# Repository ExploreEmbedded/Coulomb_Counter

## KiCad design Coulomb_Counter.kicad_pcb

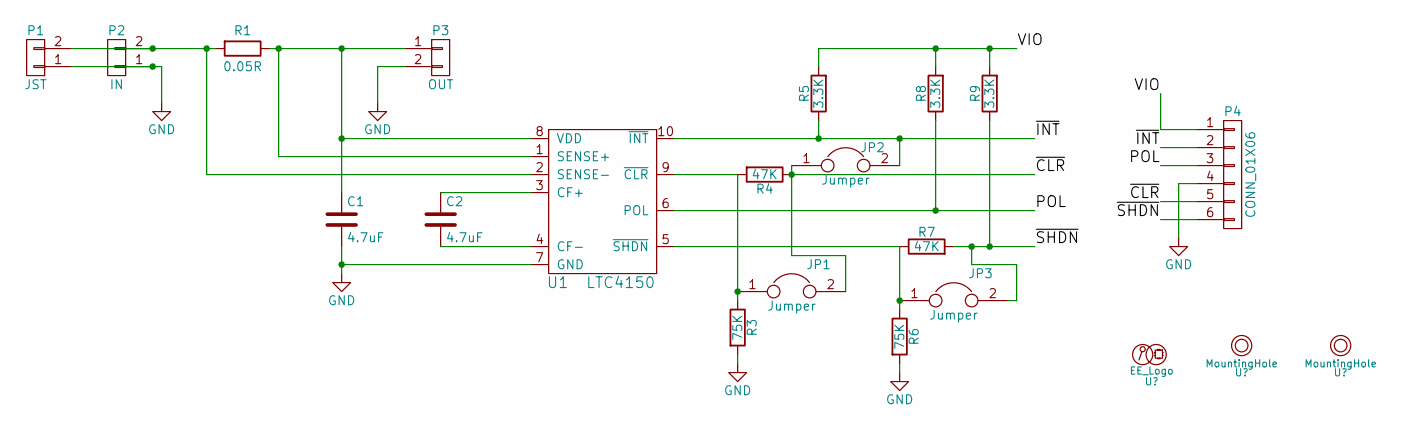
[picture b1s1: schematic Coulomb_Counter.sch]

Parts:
C1, C2: 4.7uF; C_0603
JP1, JP2, JP3: Jumper; SMD_Jumper
P1: JST; JST_Connector_SMD
P2: IN; 2Pin_Jumper_ThroughHole
P3: OUT; 2Pin_Jumper_ThroughHole
P4: CONN_01X06; 6Pin_Burgstick
R1: 0.05R; R_1206
R3, R6: 75K; R_0603
R4, R7: 47K; R_0603
R5, R8, R9: 3.3K; R_0603
U1: LTC4150; MSOP-10_3x3mm_Pitch0.5mm

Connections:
/POL: P4.3, R8.1, U1.6 (POL)
/VIO: P4.1, R5.2, R8.2, R9.2
/~CLR: JP1.2, JP2.1, P4.5, R4.1
/~INT: JP2.2, P4.2, R5.1, U1.10 (~INT)
/~SHDN: JP3.2, P4.6, R7.2, R9.1
GND: C1.2, P1.1, P2.1, P3.2, P4.4, R3.2, R6.2, U1.7 (GND)
unnamed: C1.1, P3.1, R1.1, U1.1 (SENSE+), U1.8 (VDD)
unnamed: C2.1, U1.3 (CF+)
unnamed: C2.2, U1.4 (CF-)
unnamed: JP1.1, R3.1, R4.2, U1.9 (~CLR)
unnamed: JP3.1, R6.1, R7.1, U1.5 (~SHDN)
unnamed: P1.2, P2.2, R1.2, U1.2 (SENSE-)

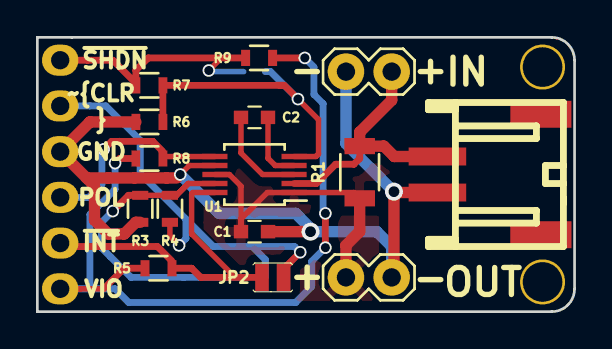
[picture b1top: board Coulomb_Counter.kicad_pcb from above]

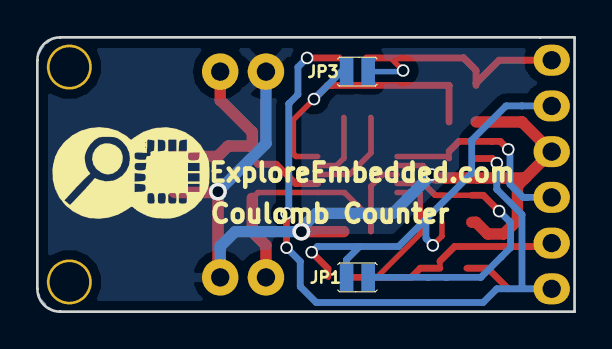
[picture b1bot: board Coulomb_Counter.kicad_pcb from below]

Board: 2 copper layers, 29.8 x 15.2 mm, 21 parts (3 on the bottom side), 12 nets.

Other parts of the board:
U2: EE_Logo; Logo_8
U3, U4: MountingHole; 1pin

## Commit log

2017-02-18 Design Files
2017-02-22 Final design
2017-02-22 Gerber file generated
